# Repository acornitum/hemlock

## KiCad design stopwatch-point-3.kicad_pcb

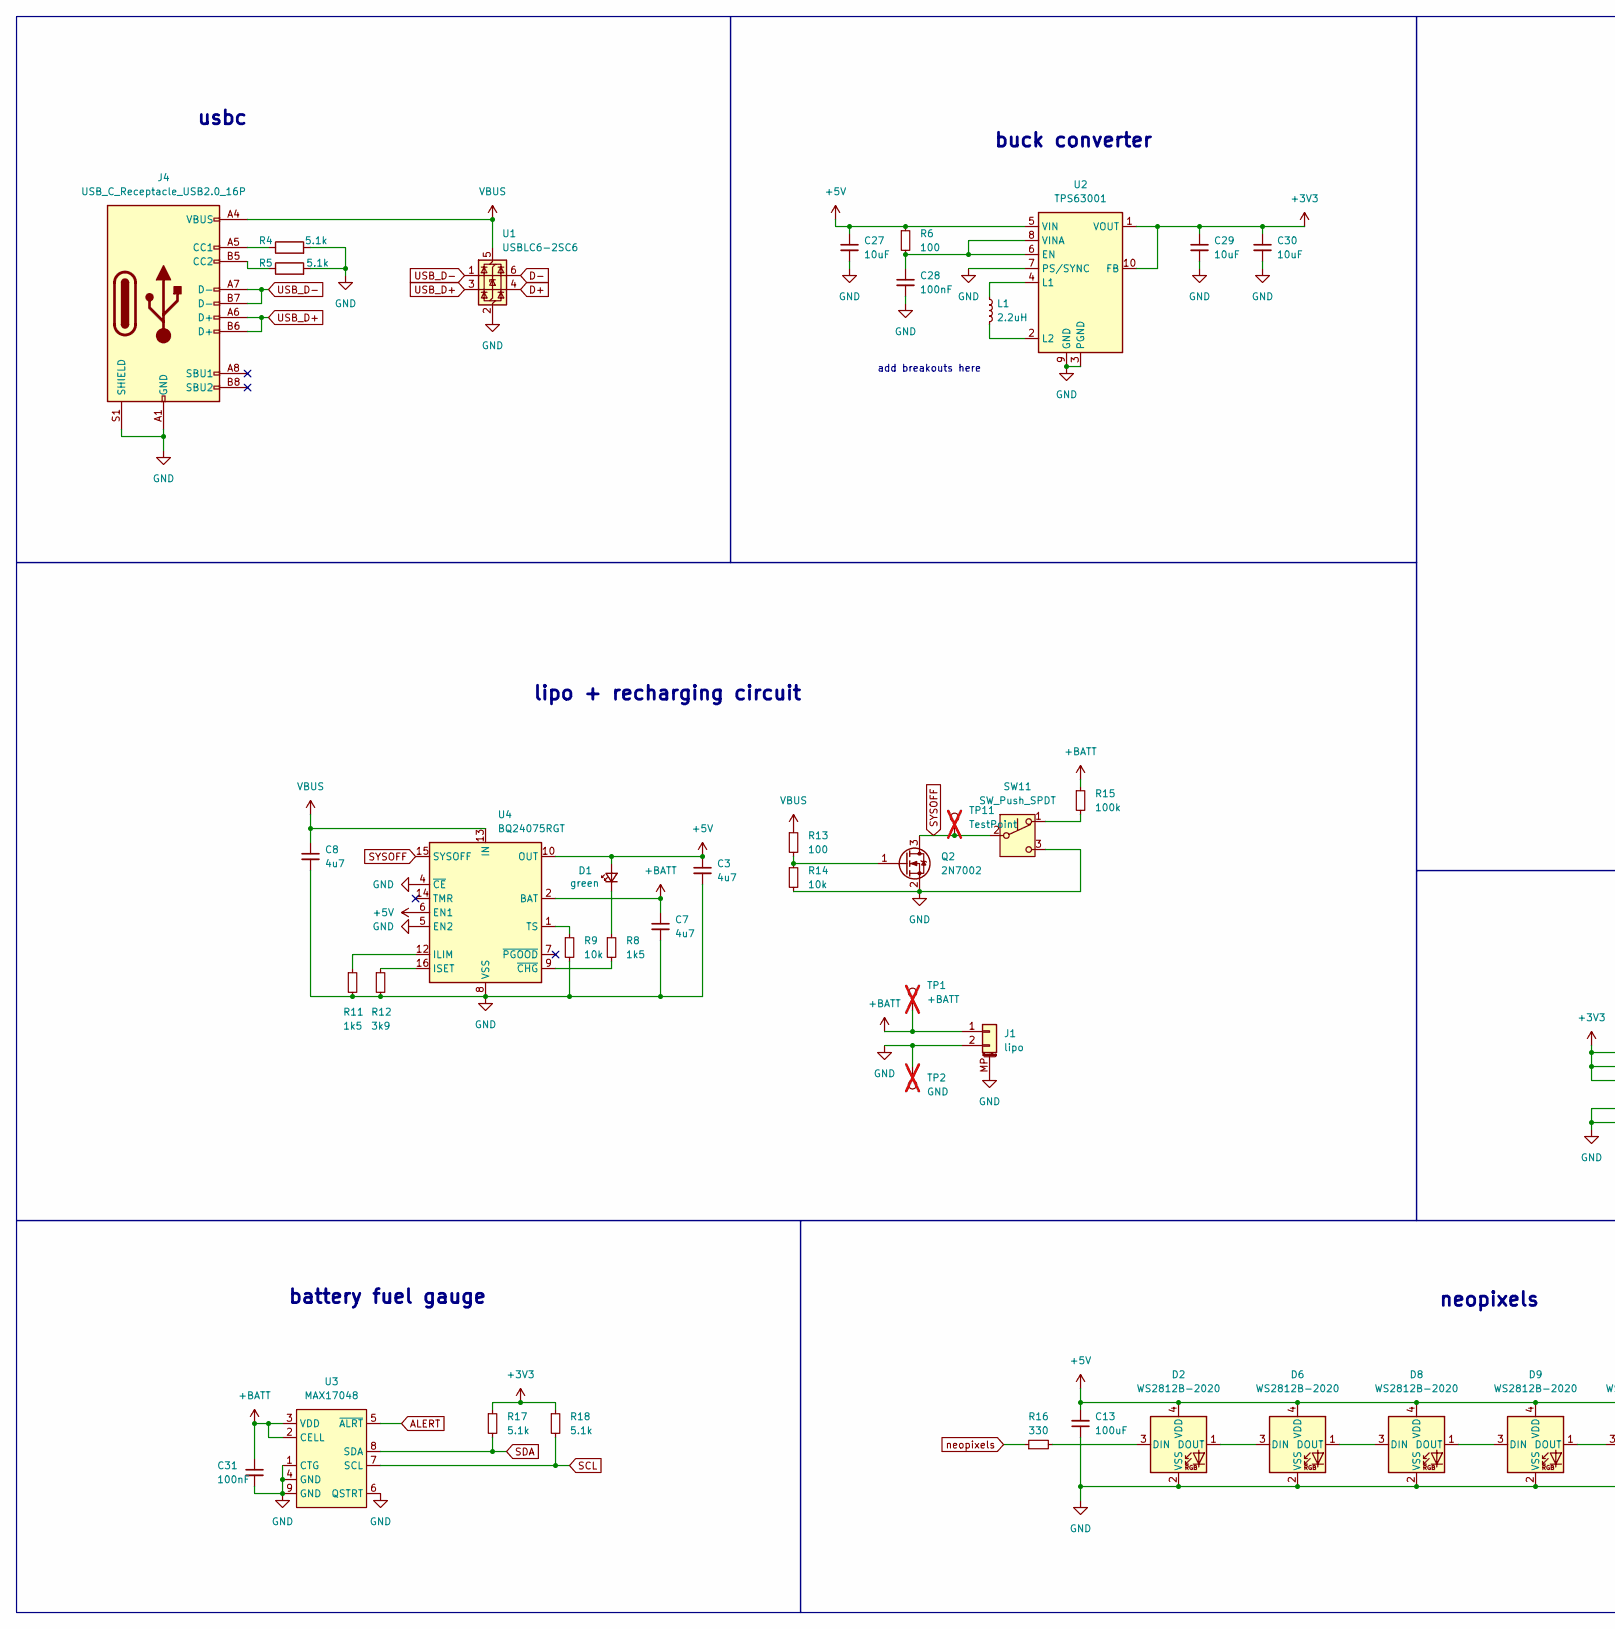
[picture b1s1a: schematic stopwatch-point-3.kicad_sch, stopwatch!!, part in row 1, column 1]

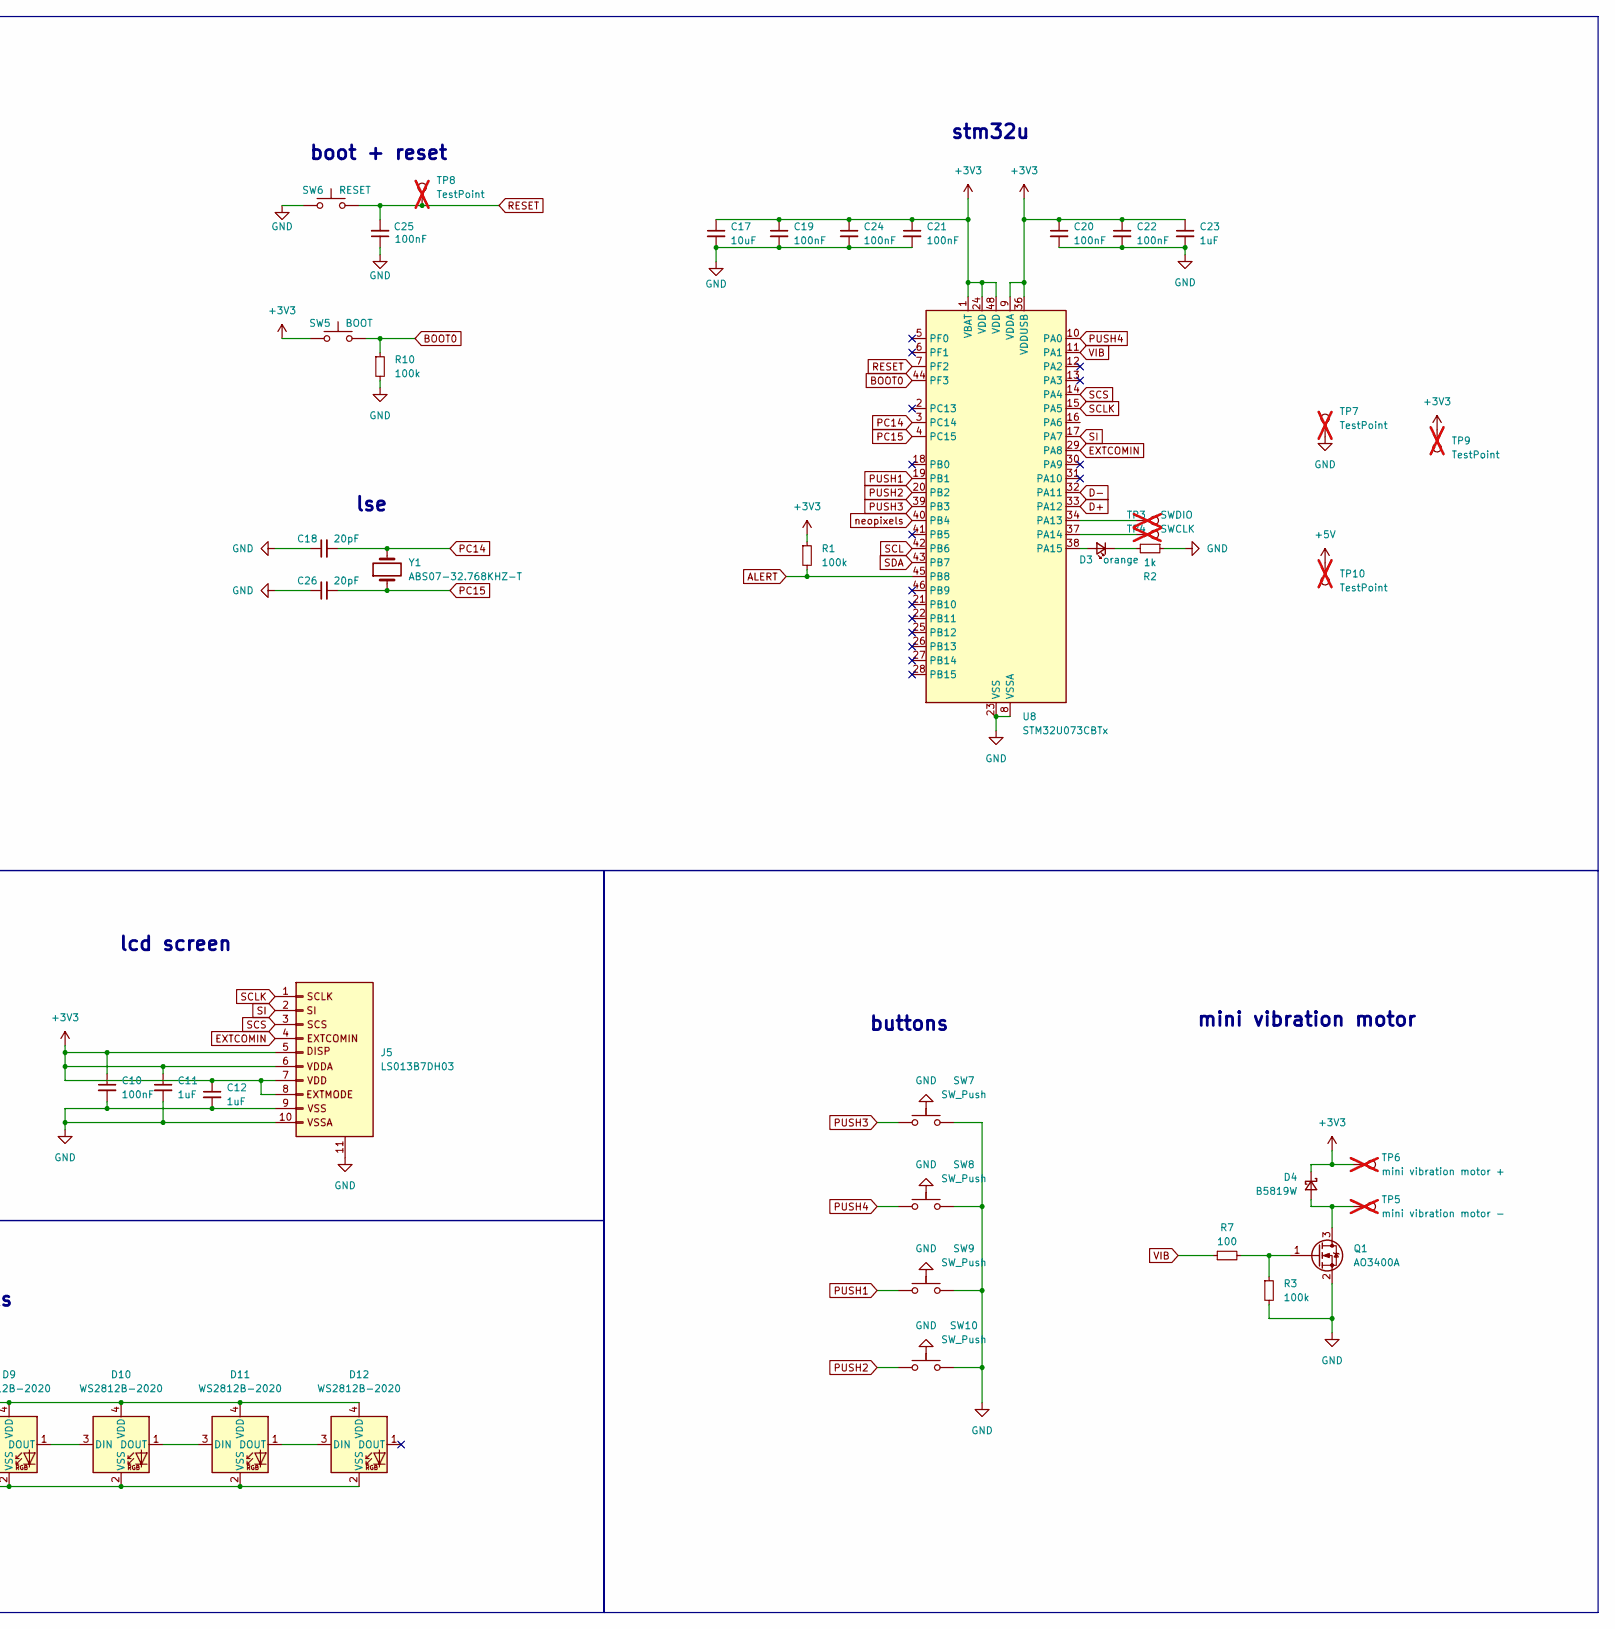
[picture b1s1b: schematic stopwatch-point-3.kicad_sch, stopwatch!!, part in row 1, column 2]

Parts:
C3, C7, C8: 4u7; C_0402_1005Metric; LCSC C368809
C10, C19, C20, C21, C22, C24, C25, C28, C31: 100nF; C_0402_1005Metric; LCSC C60474
C11, C12, C23: 1uF; C_0402_1005Metric; LCSC C29266
C13: 100uF; C_0805_2012Metric; LCSC C141660
C17, C27, C29, C30: 10uF; C_0402_1005Metric; LCSC C15525
C18, C26: 20pF; C_0402_1005Metric; LCSC C5137579
D1: green; LED_0402_1005Metric; LCSC C74338
D2, D6, D8, D9, D10, D11, D12: WS2812B-2020; LED_WS2812B-2020_PLCC4_2.0x2.0mm; LCSC C52917434
D3: orange; LED_0402_1005Metric; LCSC C28310436
D4: B5819W; D_SOD-123; LCSC C5345968
J1: lipo; JST_PH_S2B-PH-SM4-TB_1x02-1MP_P2.00mm_Horizontal; LCSC C295747
J4: USB_C_Receptacle_USB2.0_16P; USB_C_Receptacle_GCT_USB4105-xx-A_16P_TopMnt_Horizontal; LCSC C393939
J5: LS013B7DH03; AYF531035_LS013B7DH03; LCSC C425133
L1: 2.2uH; L_0805_2012Metric; LCSC C42455275
Q1: AO3400A; SOT-23; LCSC C347475
Q2: 2N7002; SOT-23; LCSC C8545
R1, R3, R10, R15: 100k; R_0402_1005Metric; LCSC C106232
R2: 1k; R_0402_1005Metric; LCSC C106235
R4, R5, R17, R18: 5.1k; R_0402_1005Metric; LCSC C104375
R6, R7, R13: 100; R_0402_1005Metric; LCSC C106232
R8, R11: 1k5; R_0402_1005Metric; LCSC C2933074
R9, R14: 10k; R_0402_1005Metric; LCSC C60490
R12: 3k9; R_0402_1005Metric; LCSC C2909346
R16: 330; R_0402_1005Metric; LCSC C2930002
SW5: BOOT; SW_Push_SPST_NO_Alps_SKRK; LCSC C720477
SW6: RESET; SW_Push_SPST_NO_Alps_SKRK; LCSC C720477
SW7, SW8, SW9, SW10: SW_Push; SW_Push_1P1T-MP_NO_Horizontal_Alps_SKRTLAE010; LCSC C110293
SW11: SW_Push_SPDT; SW_SPDT_PCM12; LCSC C2681570
TP1: +BATT; TestPoint_Pad_D2.0mm; not fitted
TP2: GND; TestPoint_Pad_2.0x2.0mm; not fitted
TP3: SWDIO; TestPoint_Pad_D1.0mm; not fitted
TP4: SWCLK; TestPoint_Pad_D1.0mm; not fitted
TP5: mini vibration motor -; TestPoint_Pad_2.0x2.0mm; not fitted
TP6: mini vibration motor +; TestPoint_Pad_D2.0mm; not fitted
TP7: TestPoint; TestPoint_Pad_1.0x1.0mm; not fitted
TP8, TP9: TestPoint; TestPoint_Pad_D1.0mm; not fitted
TP10, TP11: TestPoint; TestPoint_Pad_D1.5mm; not fitted
U1: USBLC6-2SC6; SOT-23-6; LCSC C7519
U2: TPS63001; Texas_DRC0010J_ThermalVias; LCSC C28060
U3: MAX17048; DFN-8-1EP_2x2mm_P0.5mm_EP0.9x1.5mm; LCSC C2682616
U4: BQ24075RGT; VQFN-16-1EP_3x3mm_P0.5mm_EP1.6x1.6mm; LCSC BQ24075RGTR
U8: STM32U073CBTx; LQFP-48_7x7mm_P0.5mm; LCSC C27035627
Y1: ABS07-32.768KHZ-T; Crystal_SMD_2012-2Pin_2.0x1.2mm; LCSC C130253

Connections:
+3V3: C10.1, C11.1, C12.1, C17.1, C19.1, C20.1, C21.1, C22.1, C23.1, C24.1, C29.1, C30.1, D4.1 (K), J5.5 (DISP), J5.6 (VDDA), J5.7 (VDD), J5.8 (EXTMODE), R1.1, R17.1, R18.1, SW5.1, TP6.1, TP9.1, U2.1 (VOUT), U2.10 (FB), U8.1 (VBAT), U8.9 (VDDA), U8.24 (VDD), U8.36 (VDDUSB), U8.48 (VDD)
+5V: C3.1, C13.2, C27.1, D1.2 (A), D2.4 (VDD), D6.4 (VDD), D8.4 (VDD), D9.4 (VDD), D10.4 (VDD), D11.4 (VDD), D12.4 (VDD), R6.1, TP10.1, U2.5 (VIN), U4.6 (EN1), U4.10 (OUT), U4.11 (OUT)
+BATT: C7.1, C31.1, J1.1, R15.1, TP1.1, U3.2 (CELL), U3.3 (VDD), U4.2 (BAT), U4.3 (BAT)
ALERT: R1.2, U3.5 (~ALRT), U8.45 (PB8)
BOOT0: R10.1, SW5.2, U8.44 (PF3)
D+: U1.4 (I/O2), U8.33 (PA12)
D-: U1.6 (I/O1), U8.32 (PA11)
EXTCOMIN: J5.4 (EXTCOMIN), U8.29 (PA8)
GND: C3.2, C7.2, C8.2, C10.2, C11.2, C12.2, C13.1, C17.2, C18.1, C19.2, C20.2, C21.2, C22.2, C23.2, C24.2, C25.1, C26.1, C27.2, C28.2, C29.2, C30.2, C31.2, D2.2 (VSS), D6.2 (VSS), D8.2 (VSS), D9.2 (VSS), D10.2 (VSS), D11.2 (VSS), D12.2 (VSS), J1.2, J1.MP (MountPin), J4.A1 (GND), J4.A12 (GND), J4.B1 (GND), J4.B12 (GND), J4.S1 (SHIELD), J5.9 (VSS), J5.10 (VSSA), J5.11, Q1.2 (S), Q2.2 (S), R2.1, R3.2, R4.2, R5.2, R9.2, R10.2, R11.2, R12.2, R14.2, SW6.1, SW7.2, SW7.MP, SW8.2, SW8.MP, SW9.2, SW9.MP, SW10.2, SW10.MP, SW11.3 (C), TP2.1, TP7.1, U1.2 (GND), U2.3 (PGND), U2.7 (PS/SYNC), U2.9 (GND), U2.11 (PGND), U3.1 (CTG), U3.4 (GND), U3.6 (QSTRT), U3.9 (GND), U4.4 (~CE), U4.5 (EN2), U4.8 (VSS), U4.17 (VSS), U8.8 (VSSA), U8.23 (VSS), U8.35 (VSS), U8.47 (VSS)
unnamed: D1.1 (K), R8.1
unnamed: D2.3 (DIN), R16.2
unnamed: D2.1 (DOUT), D6.3 (DIN)
unnamed: D3.2 (A), U8.38 (PA15)
unnamed: D3.1 (K), R2.2
unnamed: D4.2 (A), Q1.3 (D), TP5.1
unnamed: D6.1 (DOUT), D8.3 (DIN)
unnamed: D8.1 (DOUT), D9.3 (DIN)
unnamed: D9.1 (DOUT), D10.3 (DIN)
unnamed: D10.1 (DOUT), D11.3 (DIN)
unnamed: D11.1 (DOUT), D12.3 (DIN)
unnamed: J4.A5 (CC1), R4.1
unnamed: J4.B5 (CC2), R5.1
unnamed: Q1.1 (G), R3.1, R7.2
unnamed: Q2.1 (G), R13.2, R14.1
unnamed: R15.2, SW11.1 (A)
unnamed: C28.1, R6.2, U2.6 (EN), U2.8 (VINA)
unnamed: L1.1, U2.4 (L1)
unnamed: L1.2, U2.2 (L2)
unnamed: R11.1, U4.12 (ILIM)
unnamed: R12.1, U4.16 (ISET)
unnamed: R9.1, U4.1 (TS)
unnamed: R8.2, U4.9 (~CHG)
unnamed: TP3.1, U8.34 (PA13)
unnamed: TP4.1, U8.37 (PA14)
PC14: C18.2, U8.3 (PC14), Y1.2
PC15: C26.2, U8.4 (PC15), Y1.1
PUSH1: SW9.1, U8.19 (PB1)
PUSH2: SW10.1, U8.20 (PB2)
PUSH3: SW7.1, U8.39 (PB3)
PUSH4: SW8.1, U8.10 (PA0)
RESET: C25.2, SW6.2, TP8.1, U8.7 (PF2)
SCL: R18.2, U3.7 (SCL), U8.42 (PB6)
SCLK: J5.1 (SCLK), U8.15 (PA5)
SCS: J5.3 (SCS), U8.14 (PA4)
SDA: R17.2, U3.8 (SDA), U8.43 (PB7)
SI: J5.2 (SI), U8.17 (PA7)
SYSOFF: Q2.3 (D), SW11.2 (B), TP11.1, U4.15 (SYSOFF)
USB_D+: J4.A6 (D+), J4.B6 (D+), U1.3 (I/O2)
USB_D-: J4.A7 (D-), J4.B7 (D-), U1.1 (I/O1)
VBUS: C8.1, J4.A4 (VBUS), J4.A9 (VBUS), J4.B4 (VBUS), J4.B9 (VBUS), R13.1, U1.5 (VBUS), U4.13 (IN)
VIB: R7.1, U8.11 (PA1)
neopixels: R16.1, U8.40 (PB4)

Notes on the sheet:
battery fuel gauge
neopixels
buttons
buck converter
lipo + recharging circuit
add breakouts here
stm32u
usbc
mini vibration motor
lcd screen
boot + reset
lse

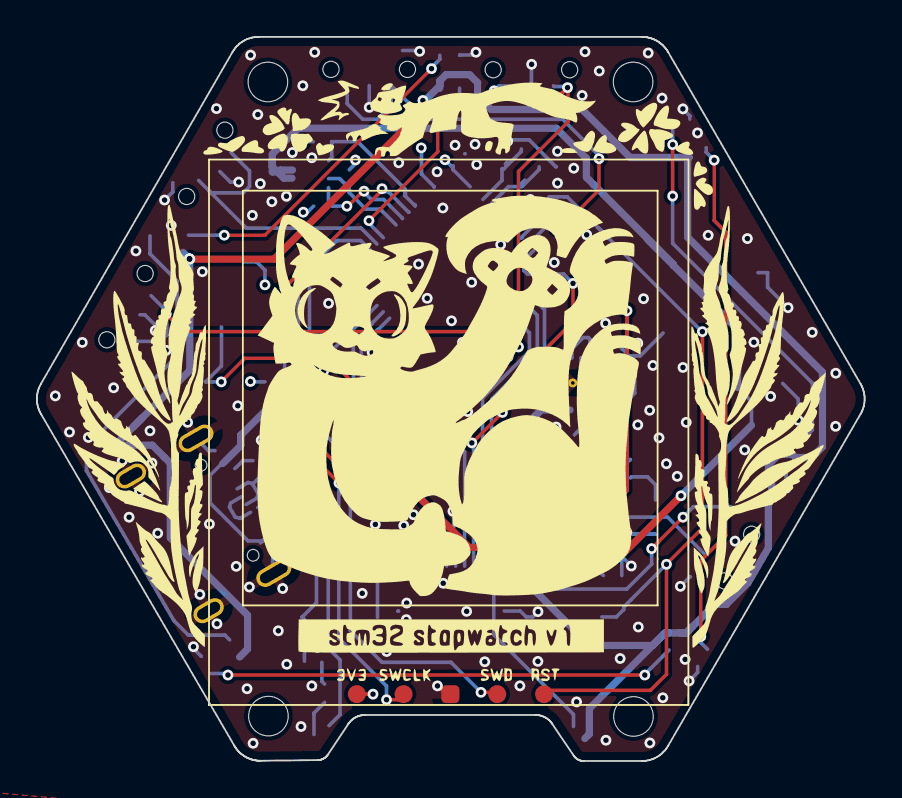
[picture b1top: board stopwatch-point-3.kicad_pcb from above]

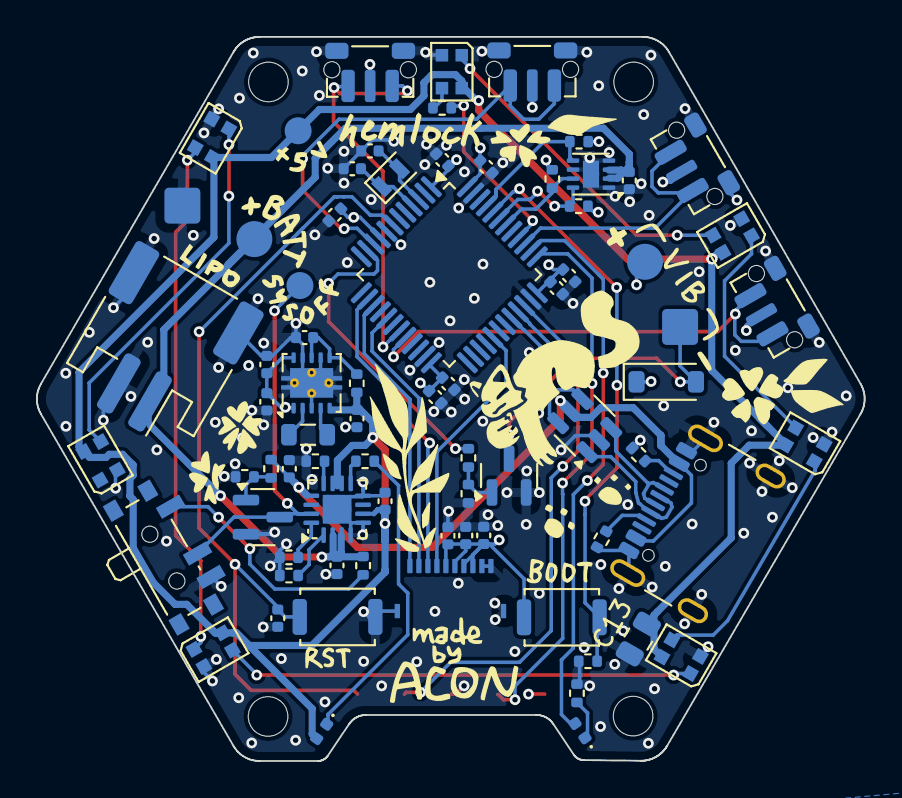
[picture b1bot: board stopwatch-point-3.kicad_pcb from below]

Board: 4 copper layers, 46.0 x 40.2 mm, 80 parts (75 on the bottom side), 52 nets.
